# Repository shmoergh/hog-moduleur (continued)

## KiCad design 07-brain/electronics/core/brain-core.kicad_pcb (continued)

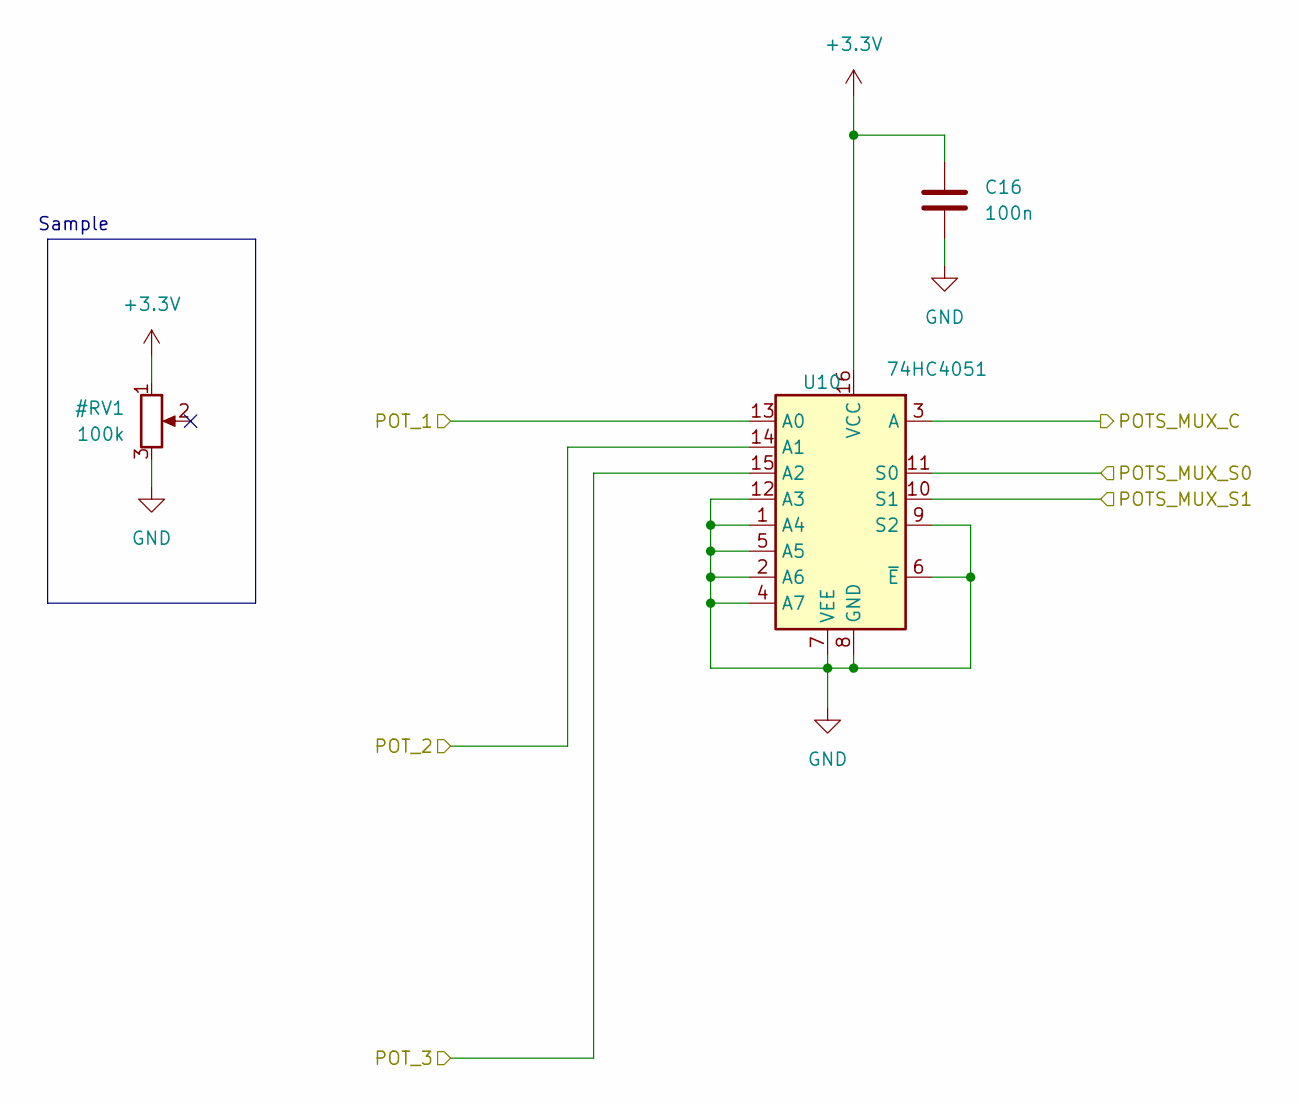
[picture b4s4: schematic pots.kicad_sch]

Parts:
C16: 100n; C_0603_1608Metric; LCSC C14663
U10: 74HC4051; SOIC-16_3.9x9.9mm_P1.27mm

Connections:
/GPIO_16: U10.11 (S0); also elsewhere on the board
/GPIO_17: U10.10 (S1); also elsewhere on the board
/GPIO_26: U10.3 (A); also elsewhere on the board
POT_1: U10.13 (A0); also elsewhere on the board
POT_2: U10.14 (A1); also elsewhere on the board
POT_3: U10.15 (A2); also elsewhere on the board

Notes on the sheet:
Sample

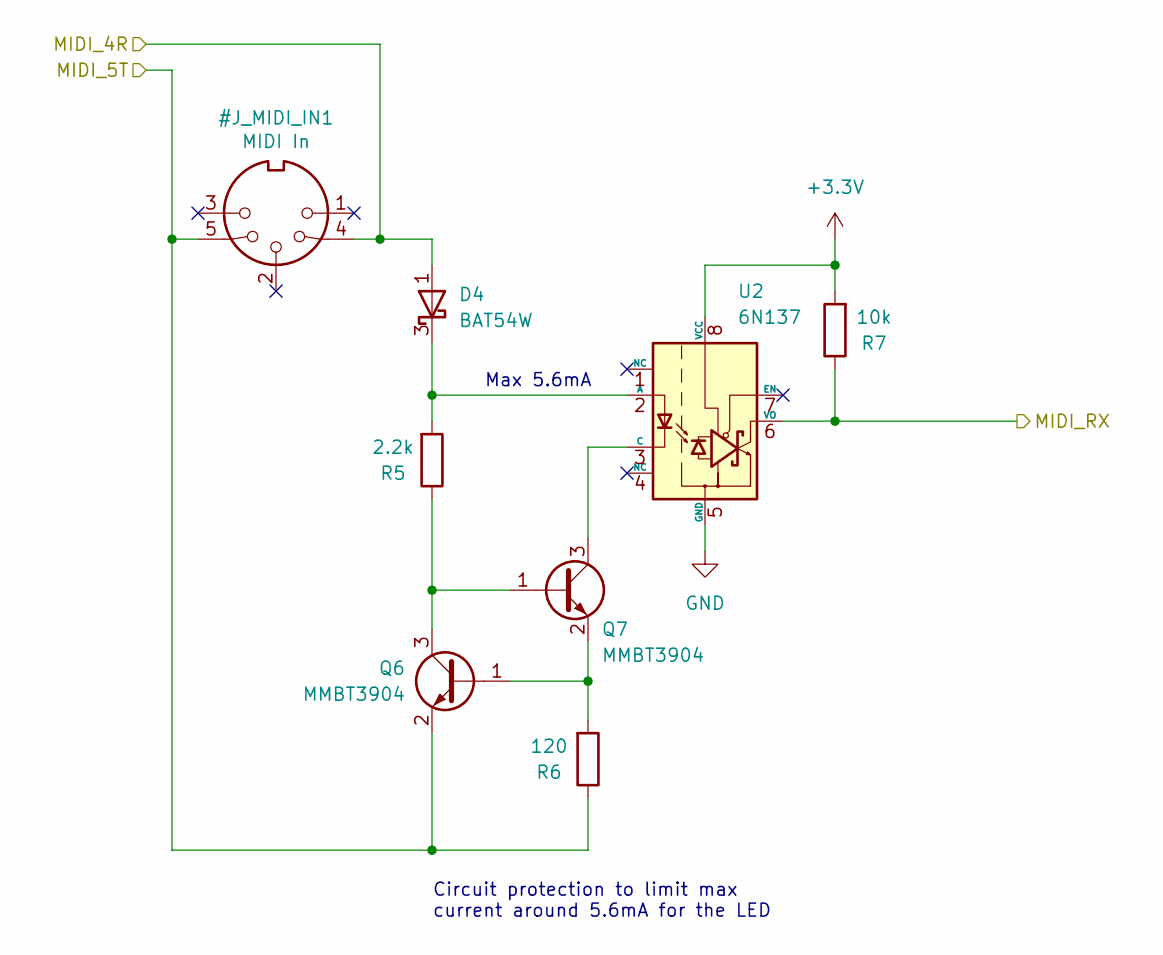
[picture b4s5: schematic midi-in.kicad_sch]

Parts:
D4: BAT54W; SOT-23
Q6, Q7: MMBT3904; SOT-23; LCSC C20526
R5: 2.2k; R_0603_1608Metric
R6: 120; R_0603_1608Metric
R7: 10k; R_0603_1608Metric
U2: 6N137; SOP-8_6.605x9.655mm_P2.54mm

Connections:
/GPIO_9: R7.1, U2.6 (VO); also elsewhere on the board
unnamed: D4.3 (K), R5.2, U2.2 (A)
unnamed: Q6.1 (B), Q7.2 (E), R6.2
unnamed: Q6.3 (C), Q7.1 (B), R5.1
unnamed: Q7.3 (C), U2.3 (C)

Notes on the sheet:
Max 5.6mA
Circuit protection to limit max current around 5.6mA for the LED

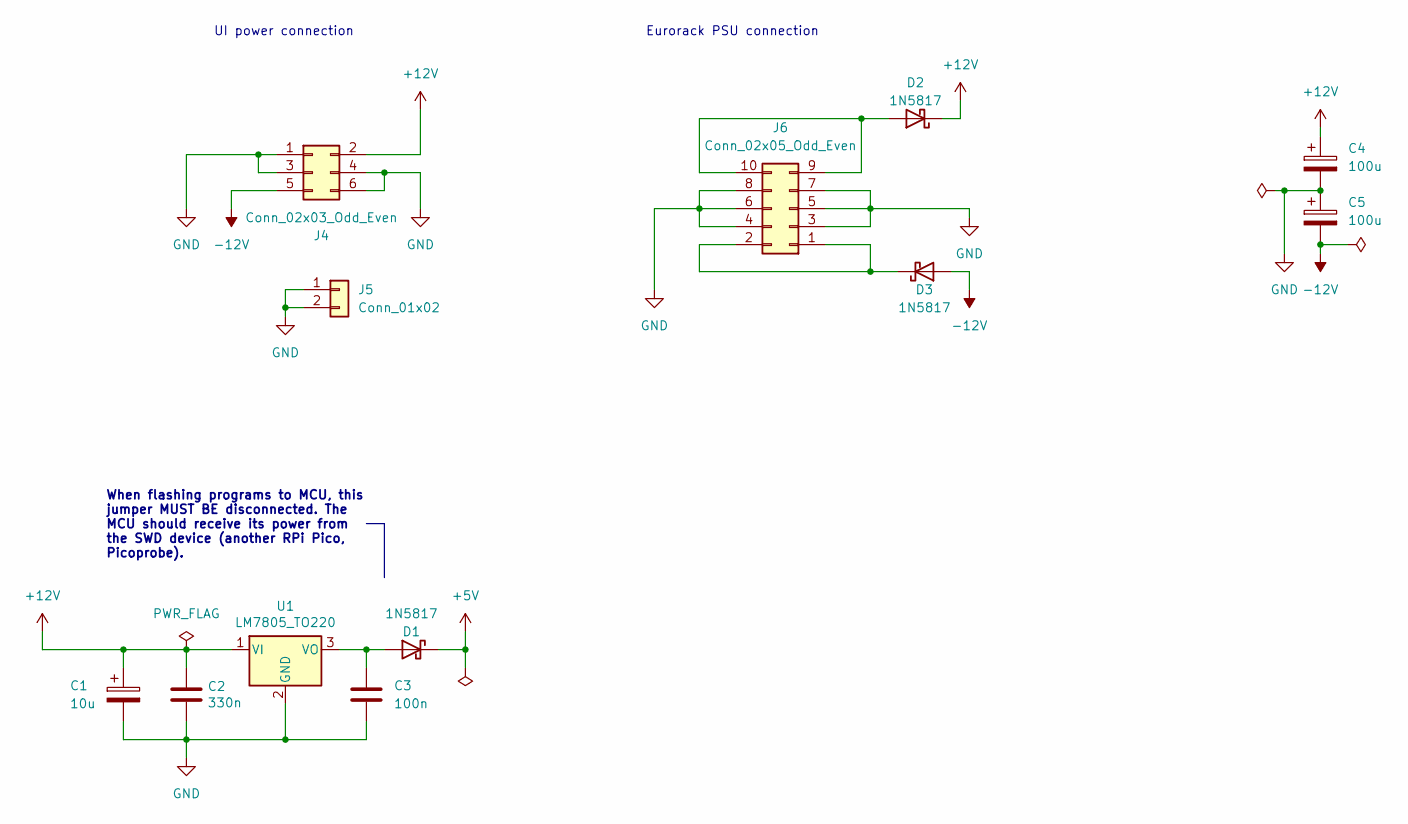
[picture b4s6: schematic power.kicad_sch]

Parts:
C1: 10u; CP_Elec_4x5.4; LCSC C46550410
C2: 330n; C_0603_1608Metric_Pad1.08x0.95mm_HandSolder; LCSC C188679
C3: 100n; C_0603_1608Metric; LCSC C14663
C4, C5: 100u; CP_Elec_6.3x7.7; LCSC C2836437
D1, D2, D3: 1N5817; D_SOD-323; LCSC C5190152
J4: Conn_02x03_Odd_Even; PinHeader_2x03_P2.54mm_Vertical
J5: Conn_01x02; PinHeader_1x02_P2.54mm_Vertical
J6: Conn_02x05_Odd_Even; IDC-Header_2x05_P2.54mm_Horizontal
U1: LM7805_TO220; TO-220-3_Horizontal_TabDown; Part No. 926-LM7805CT/NOPB

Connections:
+5V: D1.1 (K); also elsewhere on the board
+12V: C1.1, C2.1, C4.1, D2.1 (K), J4.2, U1.1 (VI); also elsewhere on the board
-12V: C5.2, D3.2 (A), J4.5; also elsewhere on the board
unnamed: C3.1, D1.2 (A), U1.3 (VO)
unnamed: D2.2 (A), J6.9, J6.10
unnamed: D3.1 (K), J6.1, J6.2

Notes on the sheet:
UI power connection
When flashing programs to MCU, this jumper MUST BE disconnected. The MCU should receive its power from the SWD device (another RPi Pico, Picoprobe).
Eurorack PSU connection

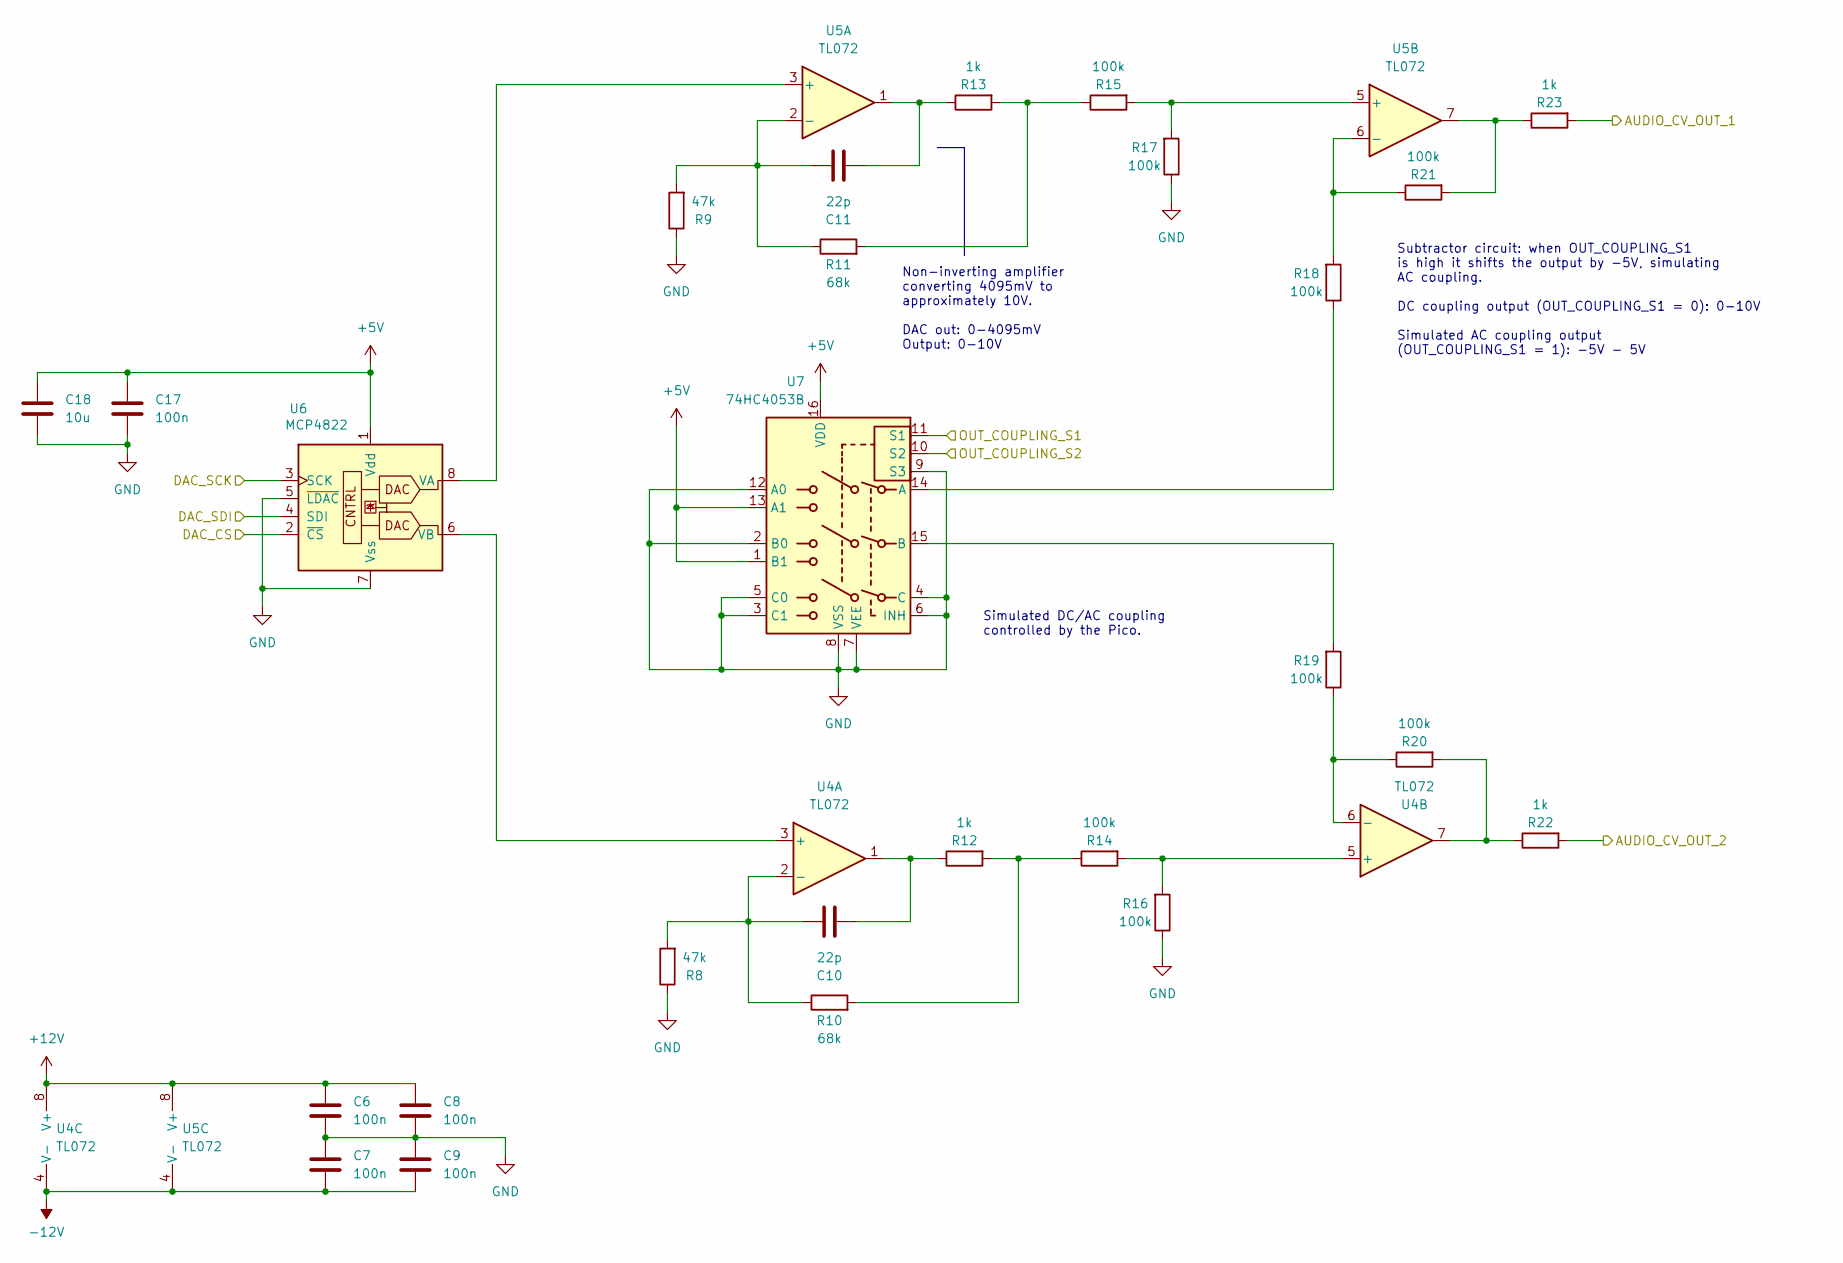
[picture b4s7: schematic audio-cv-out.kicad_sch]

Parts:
C6, C7, C8, C9, C17: 100n; C_0603_1608Metric; LCSC C14663
C10, C11: 22p; C_0603_1608Metric
C18: 10u; C_0603_1608Metric; LCSC C19702
R8, R9: 47k; R_0603_1608Metric
R10, R11: 68k; R_0603_1608Metric
R12, R13, R22, R23: 1k; R_0603_1608Metric
R14, R15, R16, R17, R18, R19, R20, R21: 100k; R_0603_1608Metric
U4, U5: TL072; SOIC-8_3.9x4.9mm_P1.27mm
U6: MCP4822; SOIC-8_3.9x4.9mm_P1.27mm; Part No. 579-MCP4822-E/P
U7: 74HC4053B; SOIC-16_3.9x9.9mm_P1.27mm

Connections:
+5V: C17.1, C18.1, U6.1 (Vdd), U7.1 (B1), U7.13 (A1), U7.16 (VDD); also elsewhere on the board
+12V: C6.1, C8.1, U4.8 (V+), U5.8 (V+); also elsewhere on the board
-12V: C7.2, C9.2, U4.4 (V-), U5.4 (V-); also elsewhere on the board
/GPIO_2: U6.3 (SCK); also elsewhere on the board
/GPIO_3: U6.4 (SDI); also elsewhere on the board
/GPIO_5: U6.2 (~CS); also elsewhere on the board
/GPIO_6: U7.11 (S1); also elsewhere on the board
/GPIO_7: U7.10 (S2); also elsewhere on the board
AUDIO_CV_OUT_1: R23.2; also elsewhere on the board
AUDIO_CV_OUT_2: R22.2; also elsewhere on the board
unnamed: C10.2, R12.1, U4.1
unnamed: C11.2, R13.1, U5.1
unnamed: R10.2, R12.2, R14.1
unnamed: R11.2, R13.2, R15.1
unnamed: R20.2, R22.1, U4.7
unnamed: R21.2, R23.1, U5.7
unnamed: U4.3 (+), U6.6 (VB)
unnamed: C10.1, R8.2, R10.1, U4.2 (-)
unnamed: R14.2, R16.2, U4.5 (+)
unnamed: R19.1, R20.1, U4.6 (-)
unnamed: U5.3 (+), U6.8 (VA)
unnamed: C11.1, R9.2, R11.1, U5.2 (-)
unnamed: R15.2, R17.2, U5.5 (+)
unnamed: R18.2, R21.1, U5.6 (-)
unnamed: R18.1, U7.14 (A)
unnamed: R19.2, U7.15 (B)

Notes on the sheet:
Simulated DC/AC coupling controlled by the Pico.
Subtractor circuit: when OUT_COUPLING_S1 is high it shifts the output by -5V, simulating AC coupling. DC coupling output (OUT_COUPLING_S1 = 0): 0-10V Simulated AC coupling output (OUT_COUPLING_S1 = 1): -5V - 5V
Non-inverting amplifier converting 4095mV to approximately 10V. DAC out: 0-4095mV Output: 0-10V

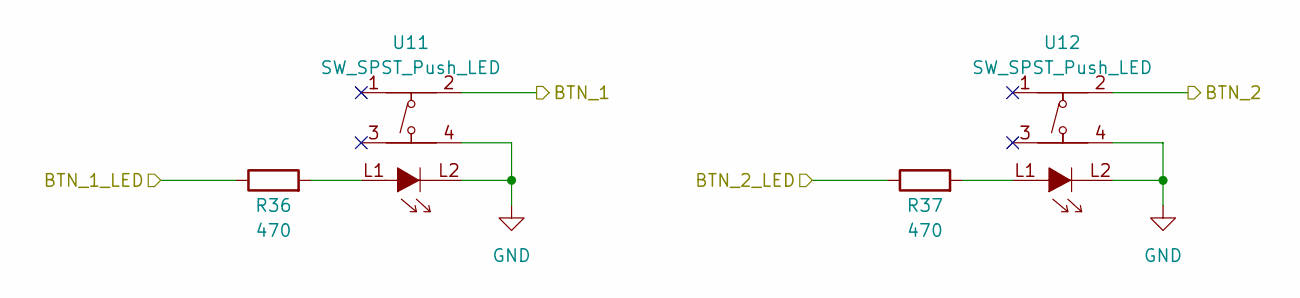
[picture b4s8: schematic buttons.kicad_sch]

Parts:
R36, R37: 470; R_0603_1608Metric
U11, U12: SW_SPST_Push_LED; SPST_Circular_Pushbutton_LED

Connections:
unnamed 44: R36.1; also elsewhere on the board
unnamed 45: R37.1; also elsewhere on the board
unnamed: U11.4, U11.L2, U12.4, U12.L2

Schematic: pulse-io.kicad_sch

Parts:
Q1, Q3: MMBT3904; SOT-23; LCSC C20526
R1, R2: 100k; R_0603_1608Metric; LCSC C25803
R3: 10k; R_0603_1608Metric; LCSC C25804
R4: 7.5k; R_0603_1608Metric; LCSC C23234

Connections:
+12V: R3.2; also elsewhere on the board
/GPIO_4: Q1.3 (C); also elsewhere on the board
/GPIO_8: R2.1; also elsewhere on the board
unnamed: Q1.1 (B), R1.2
unnamed: Q3.1 (B), R2.2
PULSE_IN: R1.1; also elsewhere on the board
PULSE_OUT: Q3.3 (C), R3.1, R4.2; also elsewhere on the board

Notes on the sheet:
About 5.1V pulses
Use Pico's pull up resistor to set value to logical 1. On pulse in, it goes to 0.
Pulse is inverted. Since the input is inverted too, if you just want to let pulses through you don't need to invert anything.

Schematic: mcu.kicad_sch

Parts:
J11: Conn_01x01; PinHeader_1x01_P2.54mm_Vertical
J13: Conn_01x03; PinHeader_1x03_P2.54mm_Vertical
J_USB_C_EXTENSION1: USB_C_Receptacle_USB2.0_16P; USB_C_Receptacle_HRO_TYPE-C-31-M-12; LCSC C165948
R36, R37: 5.1k; R_0603_1608Metric; LCSC C23186
SW1: SW_SPST; SW_Tactile_SKHH_Angled
U3: Pico; RaspberryPi_Pico_Common_Unspecified

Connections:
+5V: U3.39 (VSYS); also elsewhere on the board
/GPIO_2: U3.4 (GPIO2); also elsewhere on the board
/GPIO_3: U3.5 (GPIO3); also elsewhere on the board
/GPIO_4: U3.6 (GPIO4); also elsewhere on the board
/GPIO_5: U3.7 (GPIO5); also elsewhere on the board
/GPIO_6: U3.9 (GPIO6); also elsewhere on the board
/GPIO_7: U3.10 (GPIO7); also elsewhere on the board
/GPIO_8: U3.11 (GPIO8); also elsewhere on the board
/GPIO_9: U3.12 (GPIO9); also elsewhere on the board
/GPIO_16: U3.22 (GPIO17); also elsewhere on the board
/GPIO_17: U3.21 (GPIO16); also elsewhere on the board
/GPIO_26: U3.31 (GPIO26_ADC0); also elsewhere on the board
/GPIO_27: U3.32 (GPIO27_ADC1); also elsewhere on the board
/GPIO_28: U3.34 (GPIO28_ADC2); also elsewhere on the board
/MCU/UART_RX: U3.2 (GPIO1); also elsewhere on the board
/MCU/UART_TX: U3.1 (GPIO0); also elsewhere on the board
/MCU/USBC_N: J13.1, J_USB_C_EXTENSION1.A7 (D-), J_USB_C_EXTENSION1.B7 (D-)
/MCU/USBC_P: J13.2, J_USB_C_EXTENSION1.A6 (D+), J_USB_C_EXTENSION1.B6 (D+)
BTN_1: U3.24 (GPIO18); also elsewhere on the board
BTN_2: U3.25 (GPIO19); also elsewhere on the board
BTN_LED_1: U3.26 (GPIO20); also elsewhere on the board
BTN_LED_2: U3.27 (GPIO21); also elsewhere on the board
LED_1: U3.14 (GPIO10); also elsewhere on the board
LED_2: U3.15 (GPIO11); also elsewhere on the board
LED_3: U3.16 (GPIO12); also elsewhere on the board
LED_4: U3.17 (GPIO13); also elsewhere on the board
LED_5: U3.19 (GPIO14); also elsewhere on the board
LED_6: U3.20 (GPIO15); also elsewhere on the board
unnamed: J11.1, SW1.1 (A)
unnamed: J13.3, J_USB_C_EXTENSION1.A1 (GND), J_USB_C_EXTENSION1.A12 (GND), J_USB_C_EXTENSION1.B1 (GND), J_USB_C_EXTENSION1.B12 (GND)
unnamed: J_USB_C_EXTENSION1.A5 (CC1), R36.1
unnamed: J_USB_C_EXTENSION1.B5 (CC2), R37.1
unnamed: J_USB_C_EXTENSION1.A4 (VBUS), J_USB_C_EXTENSION1.A9 (VBUS), J_USB_C_EXTENSION1.B4 (VBUS), J_USB_C_EXTENSION1.B9 (VBUS), U3.40 (VBUS)

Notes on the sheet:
TP2 — USB- (USB Minus) TP3 — USB+ (USB Plus) TP1 - GND
Solder these to TP's on the Raspberry Pi Pico:

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
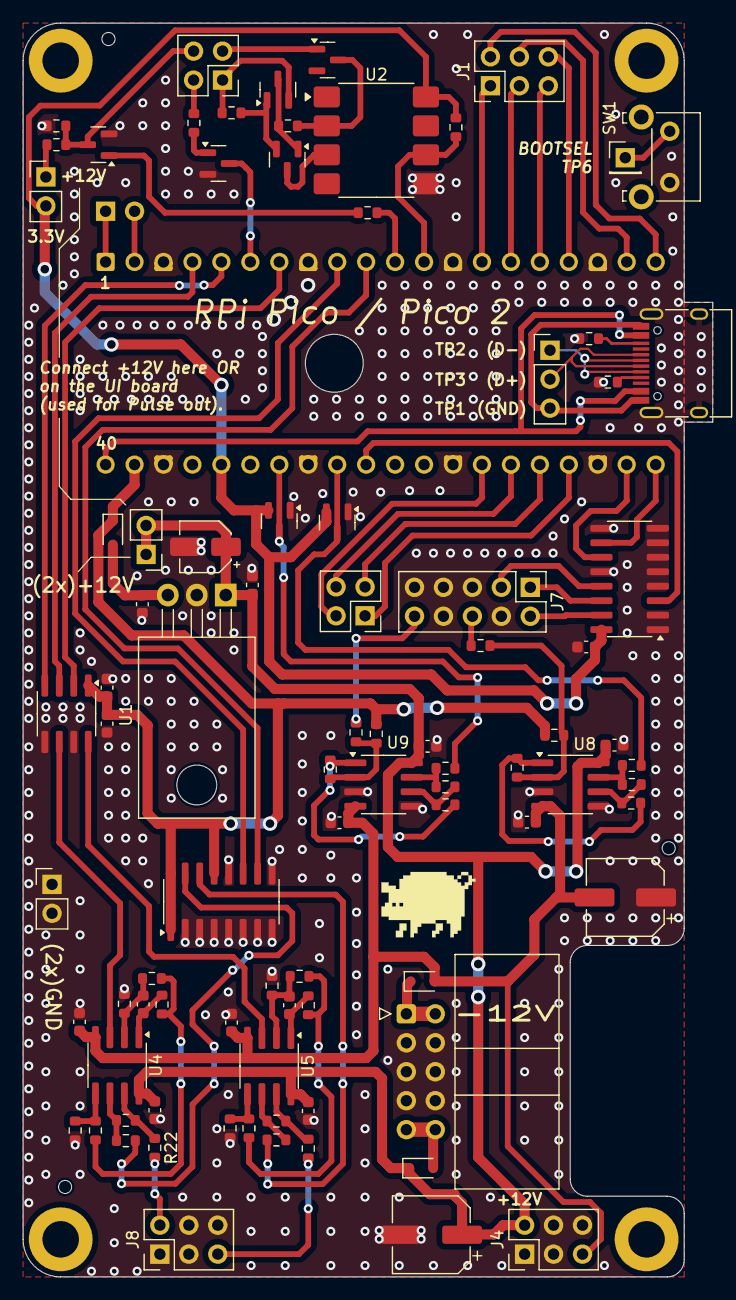
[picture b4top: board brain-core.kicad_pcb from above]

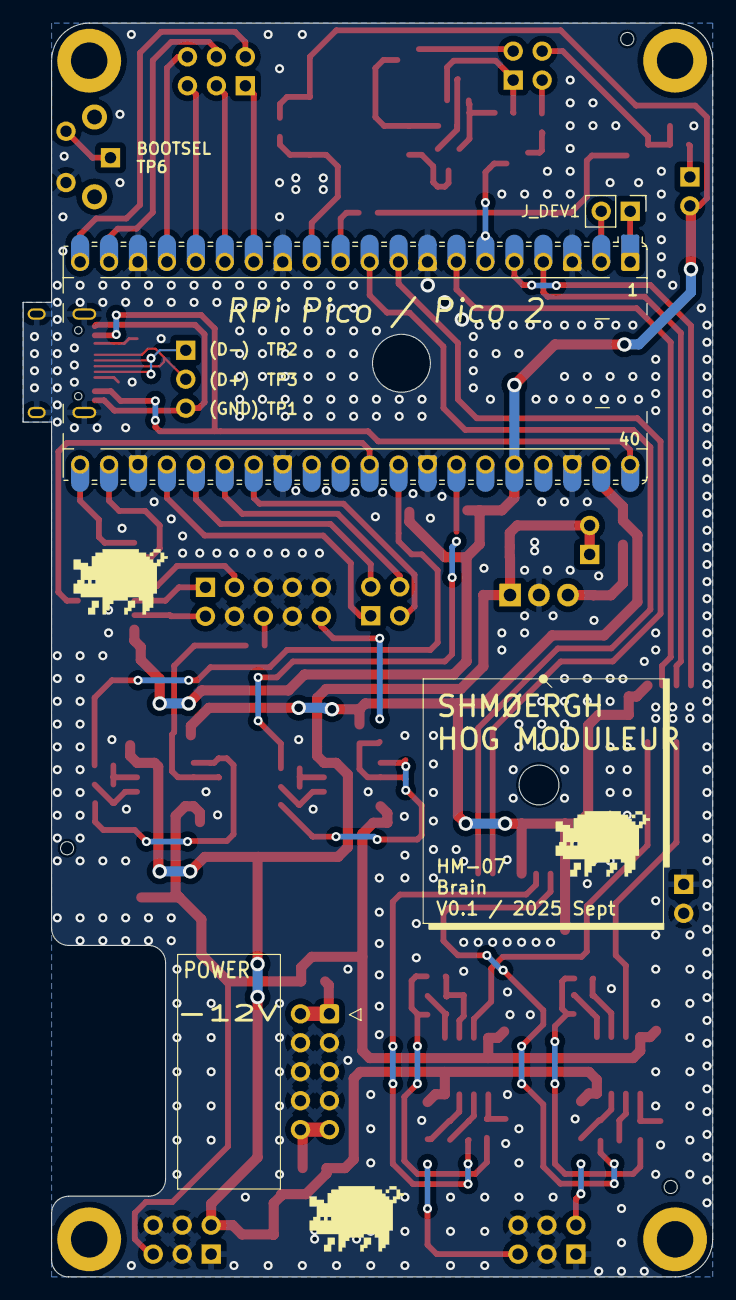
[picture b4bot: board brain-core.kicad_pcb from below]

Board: 2 copper layers, 60.5 x 110.0 mm, 94 parts (2 on the bottom side), 81 nets.

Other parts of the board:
J_DEV1: Conn_01x02; PinHeader_1x02_P2.54mm_Vertical

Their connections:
/MCU/UART_RX: J_DEV1.2; also elsewhere on the board
/MCU/UART_TX: J_DEV1.1; also elsewhere on the board

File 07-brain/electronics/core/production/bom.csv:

Designator,Footprint,Quantity,Value,LCSC Part #
C1,CP_Elec_4x5.4,1,10u,C46550410
"C10, C11",0603,2,22p,C1653
"C12, C13, C14, C15, C16, C17, C3, C6, C7, C8, C9",0603,11,100n,C14663
C18,0603,1,10u,C19702
C2,0603,1,330n,C188679
"C4, C5",CP_Elec_6.3x7.7,2,100u,C2836437
"D1, D2, D3",D_SOD-323,3,1N5817,C5190152
D4,SOT-23,1,BAT54,C22466368
"D5, D6",SOT-23,2,BAT54S,C7420333
"J1, J4, J8",PinHeader_2x03_P2.54mm_Vertical,3,Conn_02x03_Odd_Even,
"J10, J5, J9",PinHeader_1x02_P2.54mm_Vertical,3,Conn_01x02,
J11,PinHeader_1x01_P2.54mm_Vertical,1,Conn_01x01,
J13,PinHeader_1x03_P2.54mm_Vertical,1,Conn_01x03,
"J2, J3",PinHeader_2x02_P2.54mm_Vertical,2,Conn_02x02_Odd_Even,
J6,IDC-Header_2x05_P2.54mm_Horizontal,1,Conn_02x05_Odd_Even,
J7,PinHeader_2x05_P2.54mm_Vertical,1,Conn_02x05_Odd_Even,
J_USB_C_EXTENSION1,USB_C_Receptacle_HRO_TYPE-C-31-M-12,1,USB_C_Receptacle_USB2.0_16P,C165948
"Q1, Q3, Q6, Q7",SOT-23,4,MMBT3904,C20526
"R1, R14, R15, R16, R17, R18, R19, R2, R20, R21, R24, R26, R30, R31, R32, R33",0603,16,100k,C25803
"R10, R11",0603,2,68k,C23231
"R12, R13, R22, R23, R34, R35",0603,6,1k,C21190
"R25, R27",0603,2,120k,C25808
"R28, R29",0603,2,33k,C4216
"R3, R7",0603,2,10k,C25804
"R36, R37",0603,2,5.1k,C23186
R4,0603,1,7.5k,C23234
R5,0603,1,2.2k,C4190
R6,0603,1,120,C22787
"R8, R9",0603,2,47k,C25819
SW1,SW_Tactile_SKHH_Angled,1,SW_SPST,
U1,TO-220-3_Horizontal_TabDown,1,LM7805_TO220,
U10,SOIC-16_3.9x9.9mm_P1.27mm,1,74HC4051,C9386
U2,SOP-8_6.605x9.655mm_P2.54mm,1,6N137,C92651
U3,RaspberryPi_Pico_Common_Unspecified,1,Pico,
"U4, U5, U8, U9",SOIC-8_3.9x4.9mm_P1.27mm,4,TL072,C6961
U6,SOIC-8_3.9x4.9mm_P1.27mm,1,MCP4822,C623653
U7,SOIC-16_3.9x9.9mm_P1.27mm,1,74HC4053B,C5647

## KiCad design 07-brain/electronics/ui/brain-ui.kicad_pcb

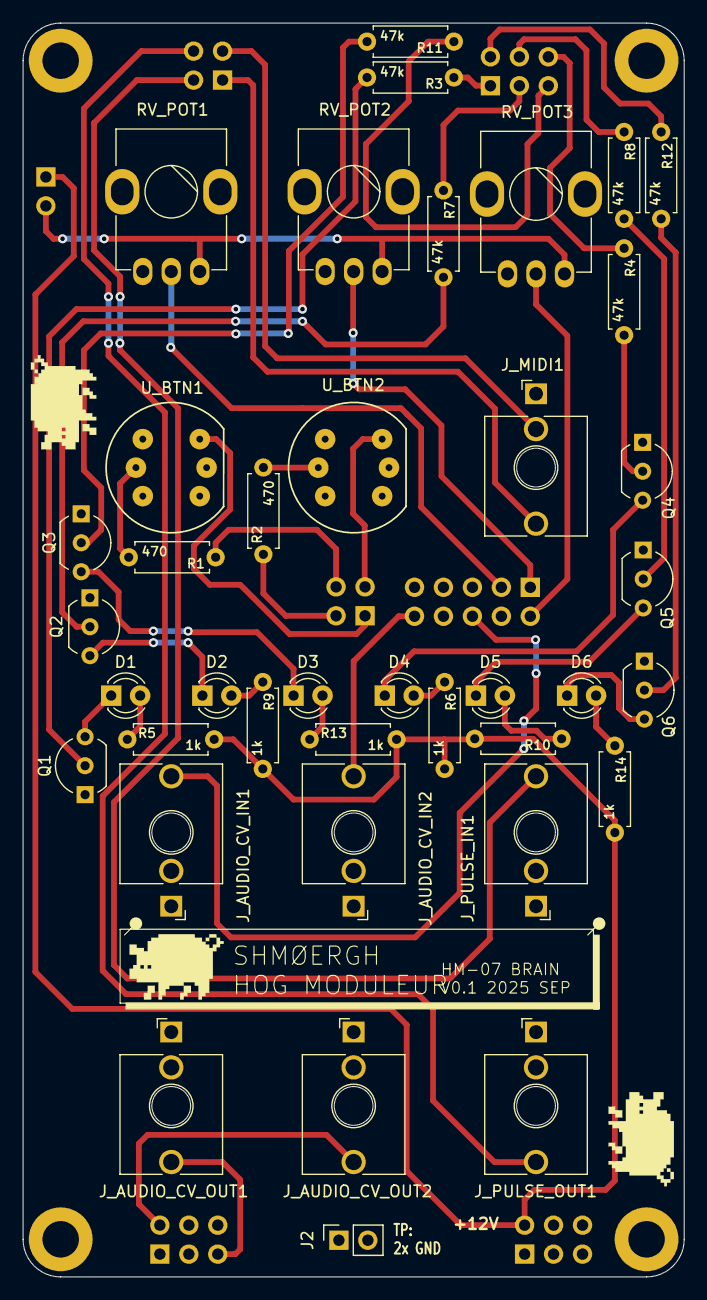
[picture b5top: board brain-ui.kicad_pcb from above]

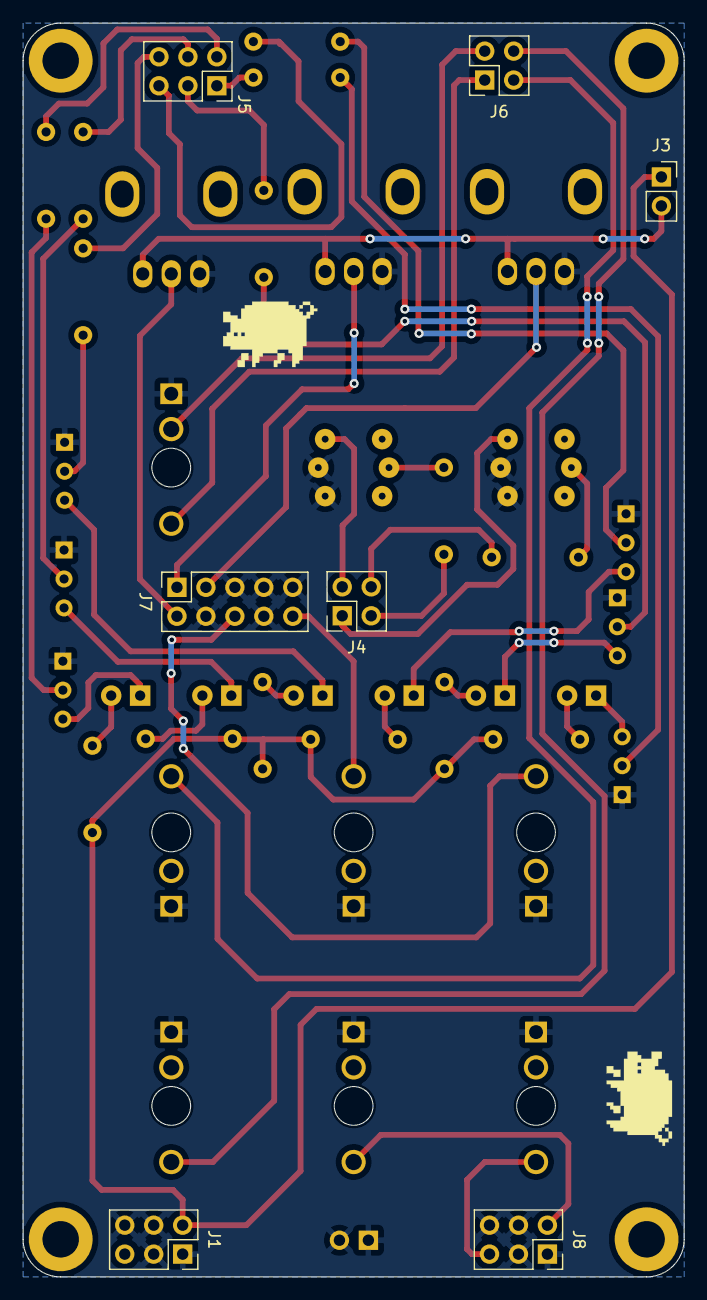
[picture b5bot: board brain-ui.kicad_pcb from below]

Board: 2 copper layers, 58.0 x 110.0 mm, 50 parts (7 on the bottom side), 44 nets.

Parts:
D1, D2, D3, D4, D5, D6: LED; LED_D3.0mm
H1, H2, H3, H4: MountingHole; MountingHole_3.2mm_M3_DIN965_Pad
J1, J5, J8: Conn_02x03_Odd_Even; PinSocket_2x03_P2.54mm_Vertical
J2, J3: Conn_01x02; PinSocket_1x02_P2.54mm_Vertical
J4, J6: Conn_02x02_Odd_Even; PinSocket_2x02_P2.54mm_Vertical
J7: Conn_02x05_Odd_Even; PinSocket_2x05_P2.54mm_Vertical
J_AUDIO_CV_IN1, J_AUDIO_CV_IN2: PJ398SM; Jack_3.5mm_QingPu_WQP-PJ398SM_Vertical_CircularHoles
J_AUDIO_CV_OUT1, J_AUDIO_CV_OUT2: PJ398SM; Jack_3.5mm_QingPu_WQP-PJ398SM_Vertical_CircularHoles
J_MIDI1: PJ398SM-STEREO; Jack_3.5mm_QingPu_WQP-PJ398SM_Vertical_CircularHoles
J_PULSE_IN1: PJ398SM; Jack_3.5mm_QingPu_WQP-PJ398SM_Vertical_CircularHoles
J_PULSE_OUT1: PJ398SM; Jack_3.5mm_QingPu_WQP-PJ398SM_Vertical_CircularHoles
Q1, Q2, Q3, Q4, Q5, Q6: 2N3904; TO-92_Inline_Wide
R1, R2: 470; R_Axial_DIN0207_L6.3mm_D2.5mm_P7.62mm_Horizontal
R3, R4, R7, R8, R11, R12: 47k; R_Axial_DIN0207_L6.3mm_D2.5mm_P7.62mm_Horizontal
R5, R6, R9, R10, R13, R14: 1k; R_Axial_DIN0207_L6.3mm_D2.5mm_P7.62mm_Horizontal
RV_POT1, RV_POT2, RV_POT3: 100k; Potentiometer_Bourns_Single-PTV09A
U_BTN1, U_BTN2: SW_SPST_Push_LED; SPST_Circular_Pushbutton_LED

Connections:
+3.3V: J3.2, RV_POT1.3, RV_POT2.3, RV_POT3.3
+12V: J1.2, J3.1, R5.2, R6.2, R9.2, R10.2, R13.2, R14.2
AUDIO_CV_IN_1: J7.6, J_AUDIO_CV_IN1.T
AUDIO_CV_IN_2: J7.10, J_AUDIO_CV_IN2.T
AUDIO_CV_OUT_1: J8.5, J_AUDIO_CV_OUT1.T
AUDIO_CV_OUT_2: J8.2, J_AUDIO_CV_OUT2.T
BTN_1: J4.1, U_BTN1.2
BTN_2: J4.3, U_BTN2.2
BTN_LED_1: J4.4, R1.1
BTN_LED_2: J4.2, R2.1
GND: J1.1, J1.3, J1.4, J1.6, J2.1, J2.2, J7.4, J7.5, J7.7, J7.8, J7.9, J8.1, J8.3, J8.4, J8.6, J_AUDIO_CV_IN1.S, J_AUDIO_CV_IN2.S, J_AUDIO_CV_OUT1.S, J_AUDIO_CV_OUT2.S, J_MIDI1.S, J_PULSE_IN1.S, J_PULSE_OUT1.S, Q1.1 (E), Q2.1 (E), Q3.1 (E), Q4.1 (E), Q5.1 (E), Q6.1 (E), RV_POT1.1, RV_POT2.1, RV_POT3.1, U_BTN1.4, U_BTN1.L2, U_BTN2.4, U_BTN2.L2
LED_1: J5.1, R3.1
LED_2: J5.3, R7.1
LED_3: J5.5, R11.1
LED_4: J5.6, R4.1
LED_5: J5.4, R8.1
LED_6: J5.2, R12.1
MIDI_4R: J6.3, J_MIDI1.TN
MIDI_5T: J6.1, J_MIDI1.T
unnamed: D1.2 (A), R5.1
unnamed: D1.1 (K), Q1.3 (C)
unnamed: D2.2 (A), R9.1
unnamed: D2.1 (K), Q2.3 (C)
unnamed: D3.2 (A), R13.1
unnamed: D3.1 (K), Q3.3 (C)
unnamed: D4.2 (A), R6.1
unnamed: D4.1 (K), Q4.3 (C)
unnamed: D5.2 (A), R10.1
unnamed: D5.1 (K), Q5.3 (C)
unnamed: D6.2 (A), R14.1
unnamed: D6.1 (K), Q6.3 (C)
unnamed: Q1.2 (B), R3.2
unnamed: Q2.2 (B), R7.2
unnamed: Q3.2 (B), R11.2
unnamed: Q4.2 (B), R4.2
unnamed: Q5.2 (B), R8.2
unnamed: Q6.2 (B), R12.2
unnamed: R1.2, U_BTN1.L1
unnamed: R2.2, U_BTN2.L1
POT_1: J7.3, RV_POT1.2
POT_2: J7.1, RV_POT2.2
POT_3: J7.2, RV_POT3.2
PULSE_IN: J6.2, J_PULSE_IN1.T
PULSE_OUT: J6.4, J_PULSE_OUT1.T
